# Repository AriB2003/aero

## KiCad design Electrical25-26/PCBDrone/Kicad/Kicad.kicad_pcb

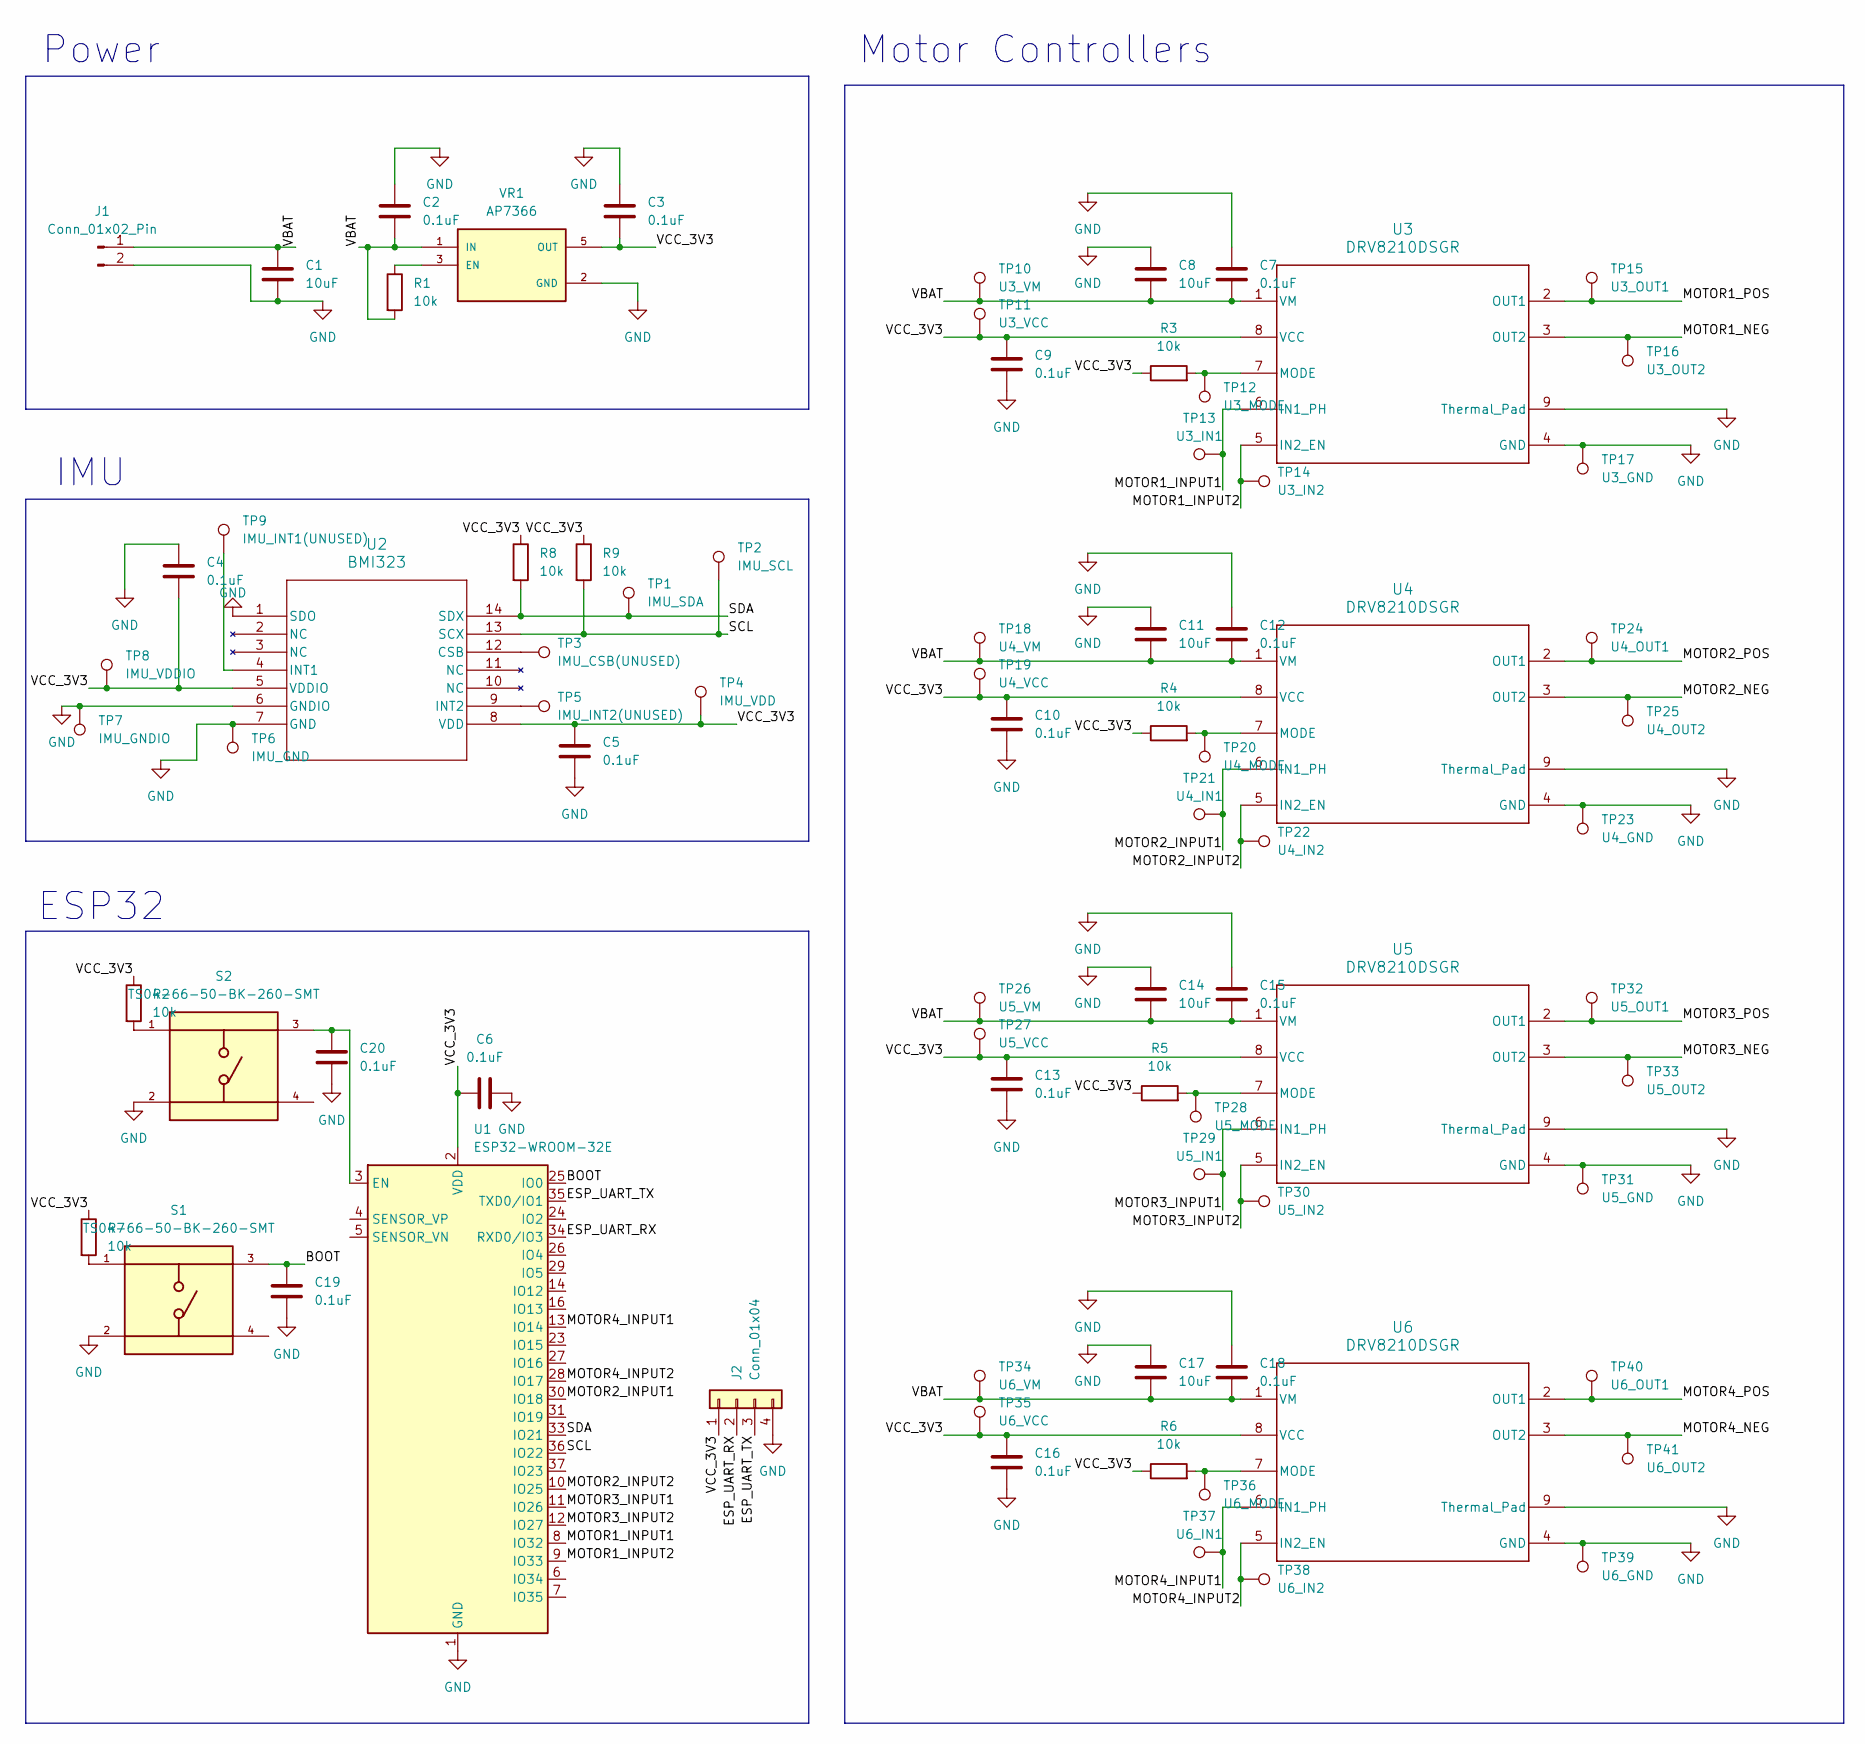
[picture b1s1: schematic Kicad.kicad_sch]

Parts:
C1, C8, C11, C14, C17: 10uF; C_0805_2012Metric
C2, C3, C4, C5, C6, C7, C9, C10, C12, C13, C15, C16, C18, C19, C20: 0.1uF; C_0603_1608Metric
J1: Conn_01x02_Pin; JST_B2B-PH-SM4-TB
J2: Conn_01x04; JST_B4B-PH-SM4-TB
R1, R2, R3, R4, R5, R6, R7, R8, R9: 10k; R_0603_1608Metric
S1, S2: TS04-66-50-BK-260-SMT; SW_TS04-66-50-BK-260-SMT; PARTREV 1.0
TP1: IMU_SDA; TestPoint_Pad_1.0x1.0mm
TP2: IMU_SCL; TestPoint_Pad_1.0x1.0mm
TP3: IMU_CSB(UNUSED); TestPoint_Pad_1.0x1.0mm
TP4: IMU_VDD; TestPoint_Pad_1.0x1.0mm
TP5: IMU_INT2(UNUSED); TestPoint_Pad_1.0x1.0mm
TP6: IMU_GND; TestPoint_Pad_1.0x1.0mm
TP7: IMU_GNDIO; TestPoint_Pad_1.0x1.0mm
TP8: IMU_VDDIO; TestPoint_Pad_1.0x1.0mm
TP9: IMU_INT1(UNUSED); TestPoint_Pad_1.0x1.0mm
TP10: U3_VM; TestPoint_Pad_1.0x1.0mm
TP11: U3_VCC; TestPoint_Pad_1.0x1.0mm
TP12: U3_MODE; TestPoint_Pad_1.0x1.0mm
TP13: U3_IN1; TestPoint_Pad_1.0x1.0mm
TP14: U3_IN2; TestPoint_Pad_1.0x1.0mm
TP15: U3_OUT1; TestPoint_Pad_1.0x1.0mm
TP16: U3_OUT2; TestPoint_Pad_1.0x1.0mm
TP17: U3_GND; TestPoint_Pad_1.0x1.0mm
TP18: U4_VM; TestPoint_Pad_1.0x1.0mm
TP19: U4_VCC; TestPoint_Pad_1.0x1.0mm
TP20: U4_MODE; TestPoint_Pad_1.0x1.0mm
TP21: U4_IN1; TestPoint_Pad_1.0x1.0mm
TP22: U4_IN2; TestPoint_Pad_1.0x1.0mm
TP23: U4_GND; TestPoint_Pad_1.0x1.0mm
TP24: U4_OUT1; TestPoint_Pad_1.0x1.0mm
TP25: U4_OUT2; TestPoint_Pad_1.0x1.0mm
TP26: U5_VM; TestPoint_Pad_1.0x1.0mm
TP27: U5_VCC; TestPoint_Pad_1.0x1.0mm
TP28: U5_MODE; TestPoint_Pad_1.0x1.0mm
TP29: U5_IN1; TestPoint_Pad_1.0x1.0mm
TP30: U5_IN2; TestPoint_Pad_1.0x1.0mm
TP31: U5_GND; TestPoint_Pad_1.0x1.0mm
TP32: U5_OUT1; TestPoint_Pad_1.0x1.0mm
TP33: U5_OUT2; TestPoint_Pad_1.0x1.0mm
TP34: U6_VM; TestPoint_Pad_1.0x1.0mm
TP35: U6_VCC; TestPoint_Pad_1.0x1.0mm
TP36: U6_MODE; TestPoint_Pad_1.0x1.0mm
TP37: U6_IN1; TestPoint_Pad_1.0x1.0mm
TP38: U6_IN2; TestPoint_Pad_1.0x1.0mm
TP39: U6_GND; TestPoint_Pad_1.0x1.0mm
TP40: U6_OUT1; TestPoint_Pad_1.0x1.0mm
TP41: U6_OUT2; TestPoint_Pad_1.0x1.0mm
U1: ESP32-WROOM-32E; ESP32-WROOM-32D
U2: BMI323; BMI323_BOS
U3, U4, U5, U6: DRV8210DSGR; DSG0008A-IPC_A
VR1: AP7366; AP7366-33W5-7; PARTREV 1-2

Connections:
/BOOT: C19.1, S1.3, U1.25 (IO0)
/ESP_UART_RX: J2.2, U1.34 (RXD0/IO3)
/ESP_UART_TX: J2.3, U1.35 (TXD0/IO1)
/MOTOR1_INPUT1: TP13.1, U1.8 (IO32), U3.6 (IN1_PH)
/MOTOR1_INPUT2: TP14.1, U1.9 (IO33), U3.5 (IN2_EN)
/MOTOR1_NEG: TP16.1, U3.3 (OUT2)
/MOTOR1_POS: TP15.1, U3.2 (OUT1)
/MOTOR2_INPUT1: TP21.1, U1.30 (IO18), U4.6 (IN1_PH)
/MOTOR2_INPUT2: TP22.1, U1.10 (IO25), U4.5 (IN2_EN)
/MOTOR2_NEG: TP25.1, U4.3 (OUT2)
/MOTOR2_POS: TP24.1, U4.2 (OUT1)
/MOTOR3_INPUT1: TP29.1, U1.11 (IO26), U5.6 (IN1_PH)
/MOTOR3_INPUT2: TP30.1, U1.12 (IO27), U5.5 (IN2_EN)
/MOTOR3_NEG: TP33.1, U5.3 (OUT2)
/MOTOR3_POS: TP32.1, U5.2 (OUT1)
/MOTOR4_INPUT1: TP37.1, U1.13 (IO14), U6.6 (IN1_PH)
/MOTOR4_INPUT2: TP38.1, U1.28 (IO17), U6.5 (IN2_EN)
/MOTOR4_NEG: TP41.1, U6.3 (OUT2)
/MOTOR4_POS: TP40.1, U6.2 (OUT1)
/SCL: R9.2, TP2.1, U1.36 (IO22), U2.13 (SCX)
/SDA: R8.2, TP1.1, U1.33 (IO21), U2.14 (SDX)
/VBAT: C1.1, C2.2, C7.2, C8.2, C11.2, C12.2, C14.2, C15.2, C17.2, C18.2, J1.1, R1.2, TP10.1, TP18.1, TP26.1, TP34.1, U3.1 (VM), U4.1 (VM), U5.1 (VM), U6.1 (VM), VR1.1 (IN)
/VCC_3V3: C3.2, C4.2, C5.1, C6.1, C9.1, C10.1, C13.1, C16.1, J2.1, R2.1, R3.1, R4.1, R5.1, R6.1, R7.1, R8.1, R9.1, TP4.1, TP8.1, TP11.1, TP19.1, TP27.1, TP35.1, U1.2 (VDD), U2.5 (VDDIO), U2.8 (VDD), U3.8 (VCC), U4.8 (VCC), U5.8 (VCC), U6.8 (VCC), VR1.5 (OUT)
GND: C1.2, C2.1, C3.1, C4.1, C5.2, C6.2, C7.1, C8.1, C9.2, C10.2, C11.1, C12.1, C13.2, C14.1, C15.1, C16.2, C17.1, C18.1, C19.2, C20.2, J1.2, J2.4, S1.2, S2.2, TP6.1, TP7.1, TP17.1, TP23.1, TP31.1, TP39.1, U1.1 (GND), U1.15 (GND), U1.38 (GND), U1.39 (GND), U2.1 (SDO), U2.6 (GNDIO), U2.7 (GND), U3.4 (GND), U3.9 (Thermal_Pad), U4.4 (GND), U4.9 (Thermal_Pad), U5.4 (GND), U5.9 (Thermal_Pad), U6.4 (GND), U6.9 (Thermal_Pad), VR1.2 (GND)
unnamed: R2.2, S2.1
unnamed: R7.2, S1.1
unnamed: C20.1, S2.3, U1.3 (EN)
unnamed: TP3.1, U2.12 (CSB)
unnamed: TP9.1, U2.4 (INT1)
unnamed: TP5.1, U2.9 (INT2)
unnamed: R3.2, TP12.1, U3.7 (MODE)
unnamed: R4.2, TP20.1, U4.7 (MODE)
unnamed: R5.2, TP28.1, U5.7 (MODE)
unnamed: R6.2, TP36.1, U6.7 (MODE)
unnamed: R1.1, VR1.3 (EN)

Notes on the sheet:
IMU
Motor Controllers
ESP32
Power

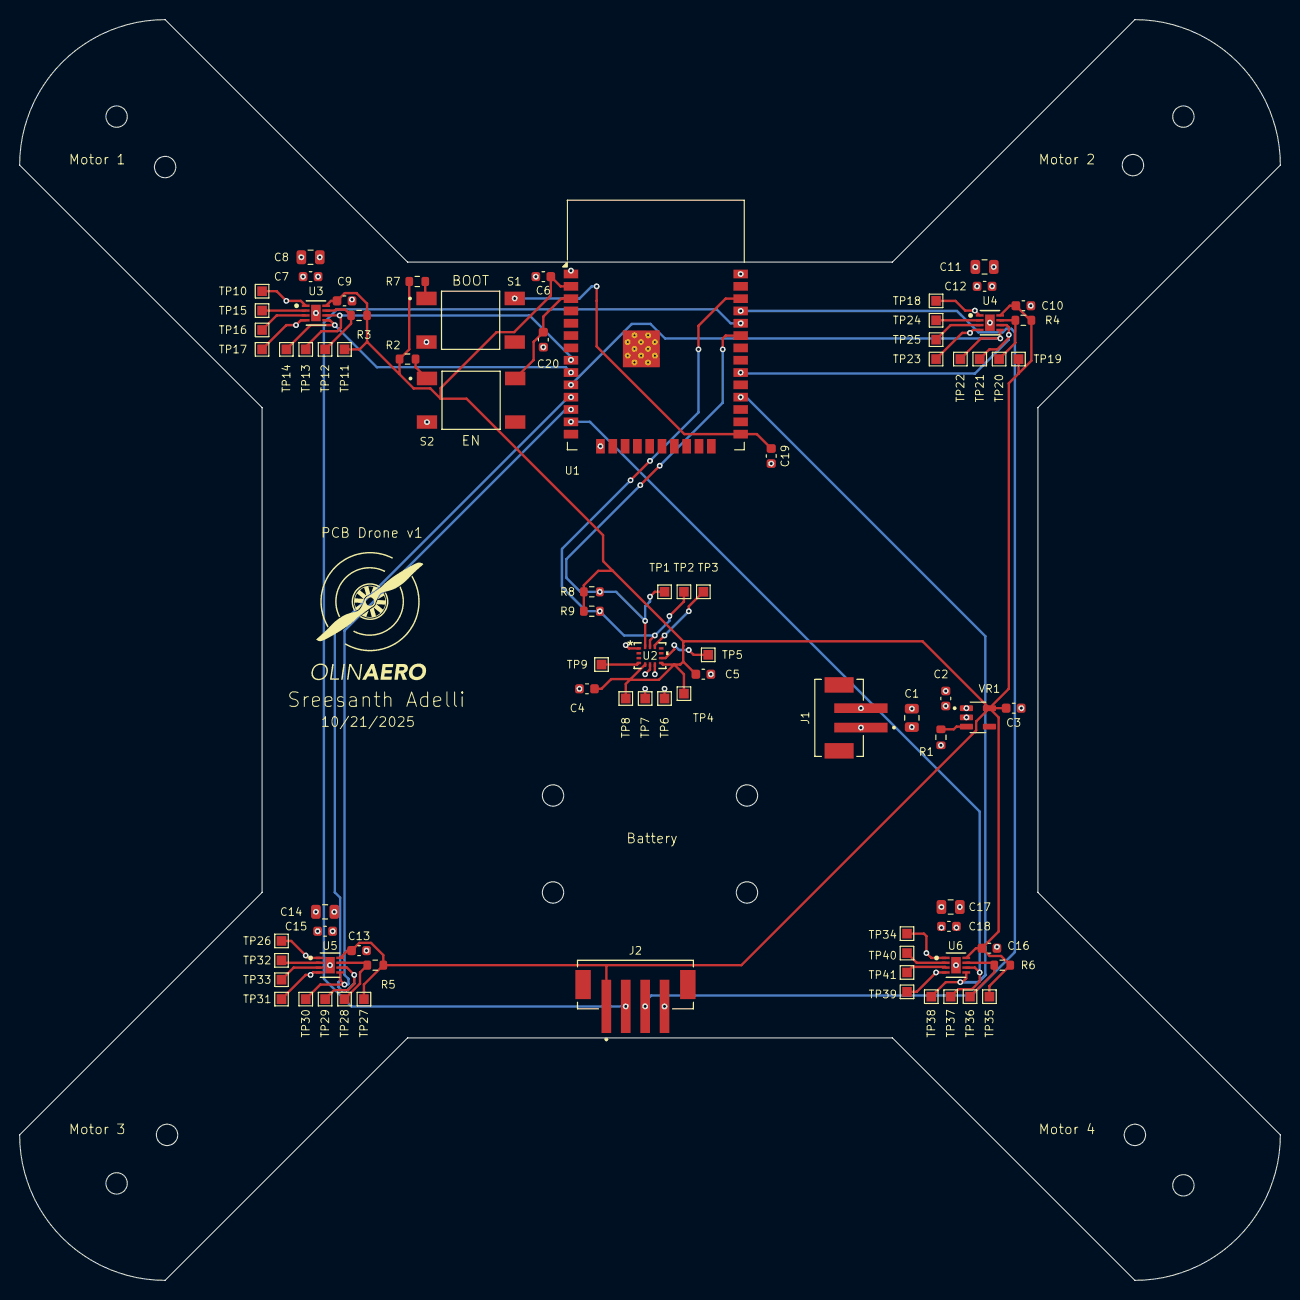
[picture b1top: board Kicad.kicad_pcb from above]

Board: 4 copper layers, 130.0 x 130.0 mm, 85 parts (0 on the bottom side), 35 nets.

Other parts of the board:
Motor Mount: Motor Mount; MotorMount
Motor Mount#2, Motor Mount#3, Motor Mount#4: Motor Mount; MotorMount

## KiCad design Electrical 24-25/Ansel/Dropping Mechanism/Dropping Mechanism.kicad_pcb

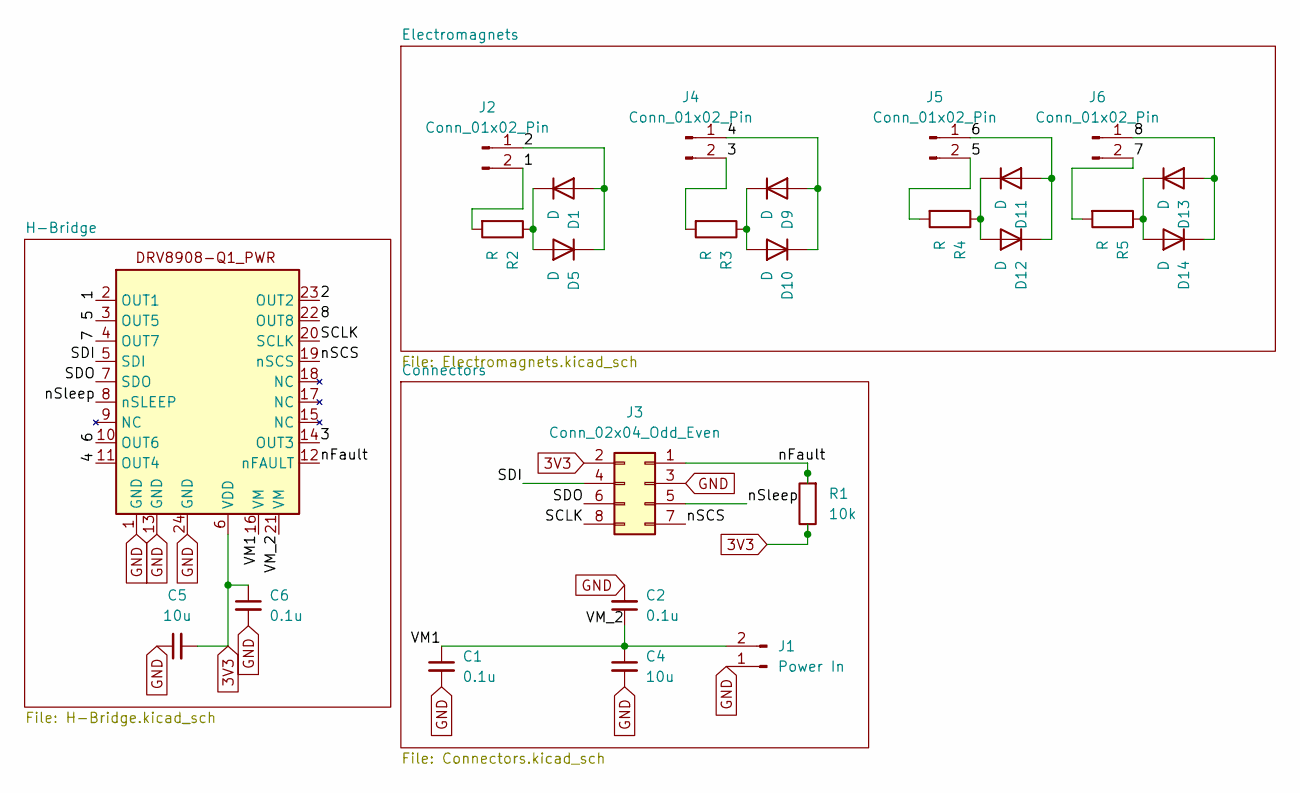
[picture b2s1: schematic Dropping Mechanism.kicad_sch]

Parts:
Automotive_Multi-Channel_Half-Bridge_Drivers_with_Advanced_Diagnostics2: HTSSOP-24-1EP_4.4x7.8mm_P0.65mm_EP3.4x7.8mm_Mask2.4x2.98mm
C1, C2, C6: 0.1u; C_0201_0603Metric
C4, C5: 10u; C_0201_0603Metric
D1, D5, D9, D10, D11, D12, D13, D14: D
J1: Power In; AMASS_XT60PW-M_1x02_P7.20mm_Horizontal
J2, J4, J5, J6: Conn_01x02_Pin; JST_XH_B2B-XH-AM_1x02_P2.50mm_Vertical
J3: Conn_02x04_Odd_Even; PinHeader_2x04_P2.54mm_Vertical
R1: 10k; R_0201_0603Metric
R2, R3, R4, R5: R

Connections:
3V3: Automotive_Multi-Channel_Half-Bridge_Dr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.6 (VDD), C5.2, C6.1, J3.2, R1.1
/1: Automotive_Multi-Channel_Half-Bridge_Dr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.2 (OUT1), J2.2, R2.2; also elsewhere on the board
/2: Automotive_Multi-Channel_Half-Bridge_Dr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.23 (OUT2), D1.2 (A), D5.1 (K), J2.1
/3: Automotive_Multi-Channel_Half-Bridge_Dr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.14 (OUT3), J4.2, R3.2
/4: Automotive_Multi-Channel_Half-Bridge_Dr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.11 (OUT4), D9.2 (A), D10.1 (K), J4.1
/5: Automotive_Multi-Channel_Half-Bridge_Dr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.3 (OUT5), J5.2, R4.2
/6: Automotive_Multi-Channel_Half-Bridge_Dr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.10 (OUT6), D11.2 (A), D12.1 (K), J5.1
/7: Automotive_Multi-Channel_Half-Bridge_Dr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.4 (OUT7), J6.2, R5.2
/8: Automotive_Multi-Channel_Half-Bridge_Dr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.22 (OUT8), D13.2 (A), D14.1 (K), J6.1
/SCLK: Automotive_Multi-Channel_Half-Bridge_Dr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.20 (SCLK), J3.8
/SDI: Automotive_Multi-Channel_Half-Bridge_Dr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.5 (SDI), J3.4
/SDO: Automotive_Multi-Channel_Half-Bridge_Dr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.7 (SDO), J3.6
/VM1: Automotive_Multi-Channel_Half-Bridge_Dr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.16 (VM), Automotive_Multi-Channel_Half-Bridge_Dr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.21 (VM), C1.1, C2.1, C4.1, J1.2
/nFault: Automotive_Multi-Channel_Half-Bridge_Dr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.12 (nFAULT), J3.1, R1.2
/nSCS: Automotive_Multi-Channel_Half-Bridge_Dr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.19 (nSCS), J3.7
/nSleep: Automotive_Multi-Channel_Half-Bridge_Dr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.8 (nSLEEP), J3.5
GND: Automotive_Multi-Channel_Half-Bridge_Dr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.1 (GND), Automotive_Multi-Channel_Half-Bridge_Dr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.13 (GND), Automotive_Multi-Channel_Half-Bridge_Dr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.24 (GND), C1.2, C2.2, C4.2, C5.1, C6.2, J1.1, J3.3
unnamed 17: D1.1 (K), D5.2 (A), R2.1; also elsewhere on the board
unnamed: D9.1 (K), D10.2 (A), R3.1
unnamed: D11.1 (K), D12.2 (A), R4.1
unnamed: D13.1 (K), D14.2 (A), R5.1

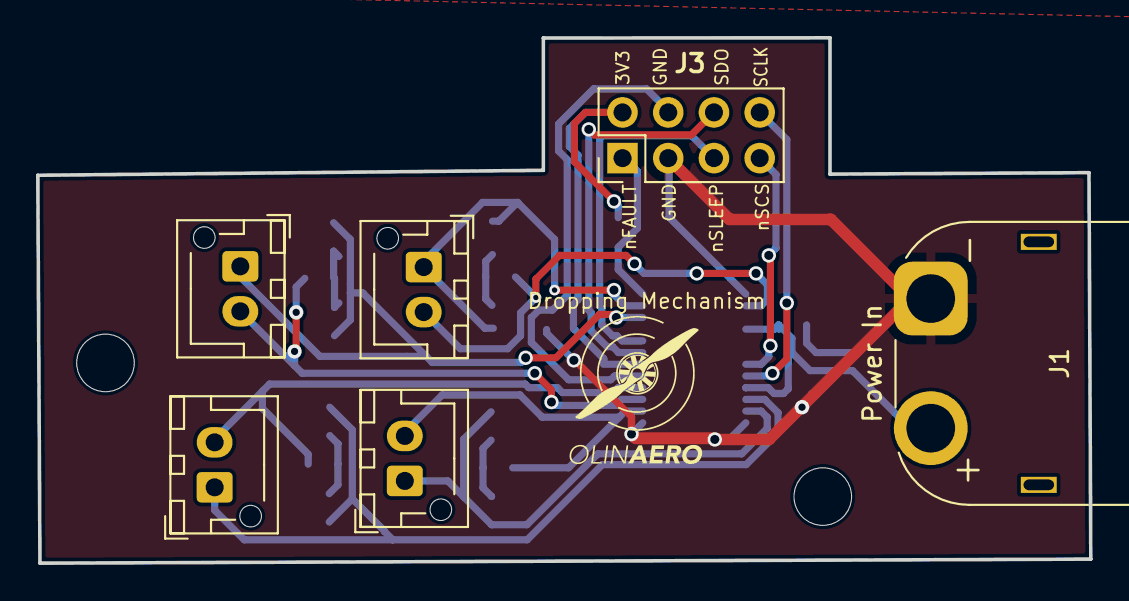
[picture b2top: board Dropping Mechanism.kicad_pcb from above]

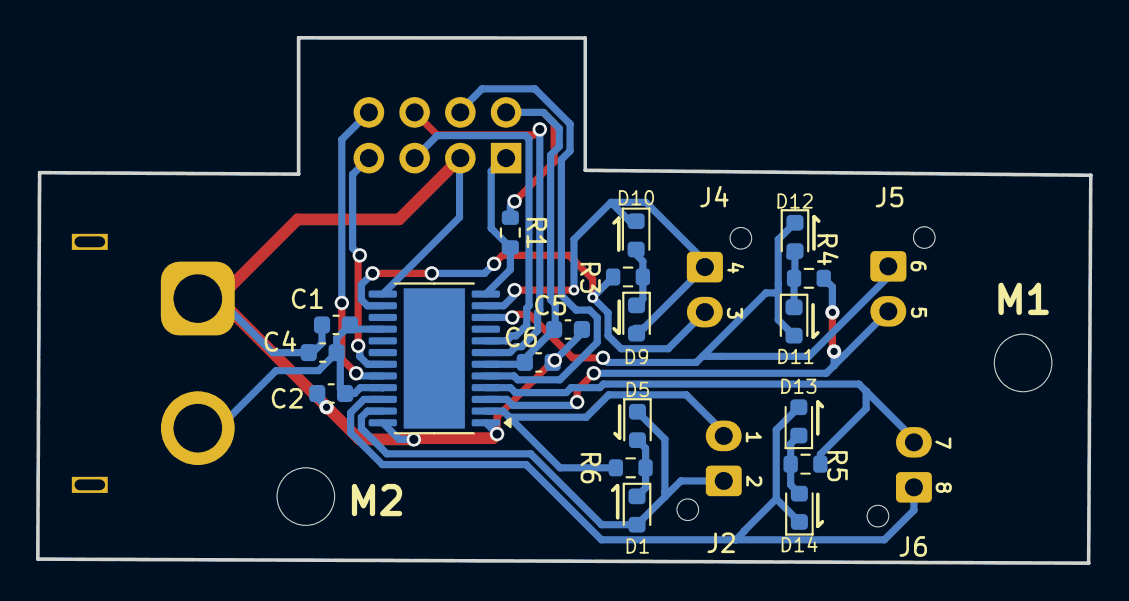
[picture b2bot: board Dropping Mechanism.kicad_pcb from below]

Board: 2 copper layers, 58.5 x 29.2 mm, 25 parts (19 on the bottom side), 21 nets.

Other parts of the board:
R6: 0.65k; R_0603_1608Metric

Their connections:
/1: R6.2; also elsewhere on the board
unnamed 17: R6.1; also elsewhere on the board

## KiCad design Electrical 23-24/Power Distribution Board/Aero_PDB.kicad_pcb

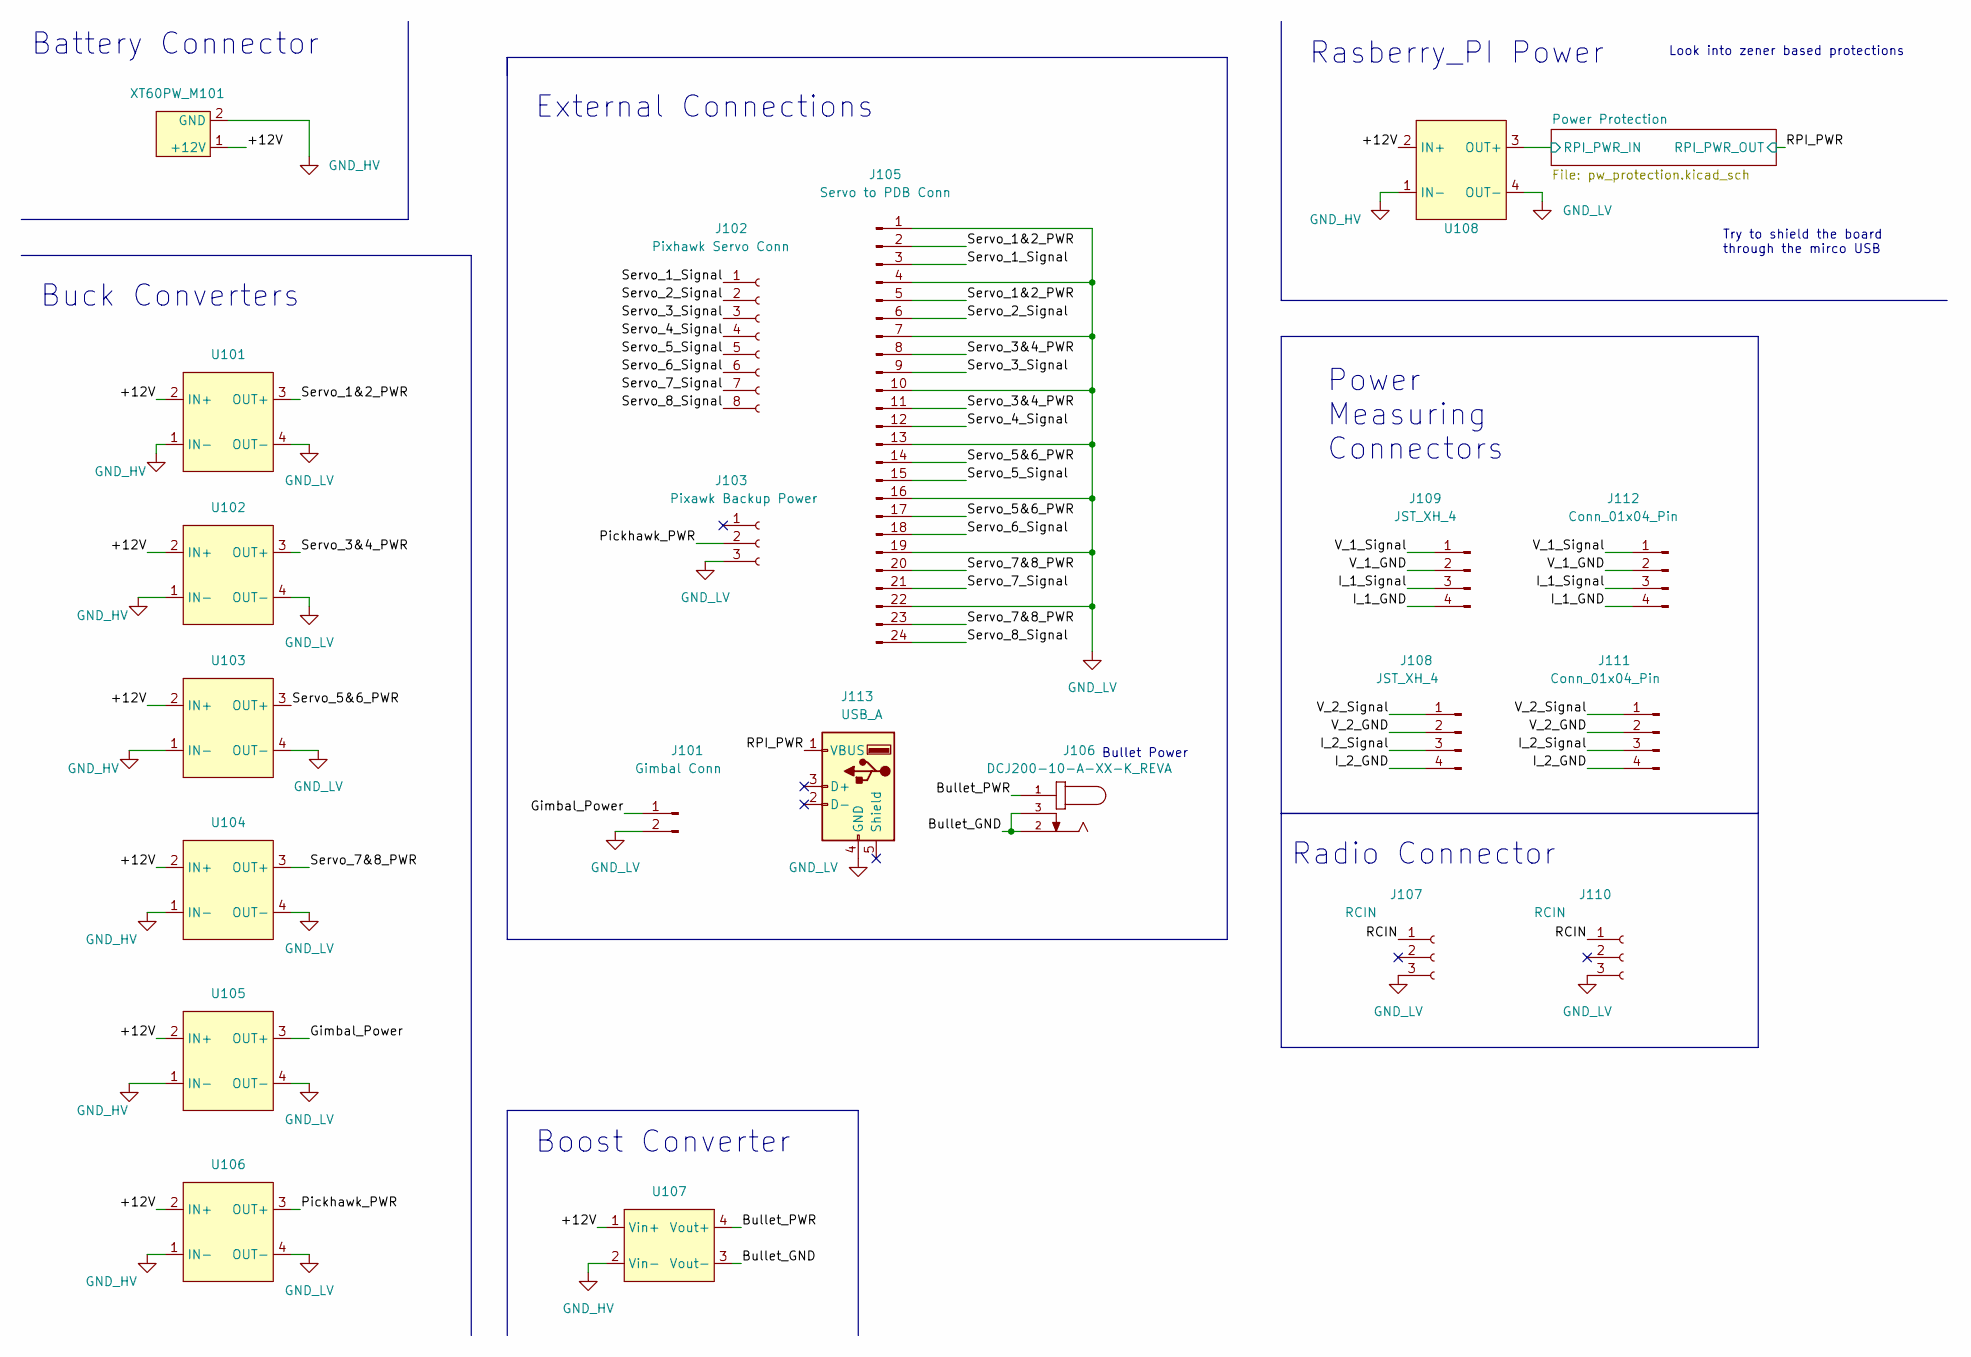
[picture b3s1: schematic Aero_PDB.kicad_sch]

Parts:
J101: Gimbal Conn; JST_XH_B2B-XH-A_1x02_P2.50mm_Vertical
J102: Pixhawk Servo Conn; PinHeader_1x08_P2.54mm_Vertical
J103: Pixawk Backup Power; PinHeader_1x03_P2.54mm_Vertical
J105: Servo to PDB Conn; SAMTEC_TSW-108-07-G-T
J106: DCJ200-10-A-XX-K_REVA; GCT_DCJ200-10-A-XX-K_REVA; PARTREV A
J107, J110: RCIN; PinHeader_1x03_P2.54mm_Vertical
J108, J109: JST_XH_4; JST_XH_B4B-XH-A_1x04_P2.50mm_Vertical
J111, J112: Conn_01x04_Pin; PinHeader_1x04_P2.54mm_Vertical
J113: USB_A; GCT_USB1130-15-A_REVA
U101, U102, U103, U104, U105, U106, U108: YAAJ_DCDC_StepDown_LM2596
U107: MT3608_module
XT60PW_M101: AMASS_XT60PW-F

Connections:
/+12V: U101.2 (IN+), U102.2 (IN+), U103.2 (IN+), U104.2 (IN+), U105.2 (IN+), U106.2 (IN+), U107.1 (Vin+), U108.2 (IN+), XT60PW_M101.1 (+12V)
/Bullet_GND: J106.2, J106.3, U107.3 (Vout-)
/Bullet_PWR: J106.1, U107.4 (Vout+)
/Gimbal_Power: J101.1, U105.3 (OUT+)
/I_1_GND: J109.4, J112.4
/I_1_Signal: J109.3, J112.3
/I_2_GND: J108.4, J111.4
/I_2_Signal: J108.3, J111.3
/Pickhawk_PWR: J103.2, U106.3 (OUT+)
/Power Protection /RPI_PWR_IN: U108.3 (OUT+); also elsewhere on the board
/RCIN: J107.1, J110.1
/RPI_PWR: J113.1 (VBUS); also elsewhere on the board
/Servo_1&2_PWR: J105.2, J105.5, U101.3 (OUT+)
/Servo_1_Signal: J102.1, J105.3
/Servo_2_Signal: J102.2, J105.6
/Servo_3&4_PWR: J105.8, J105.11, U102.3 (OUT+)
/Servo_3_Signal: J102.3, J105.9
/Servo_4_Signal: J102.4, J105.12
/Servo_5&6_PWR: J105.14, J105.17, U103.3 (OUT+)
/Servo_5_Signal: J102.5, J105.15
/Servo_6_Signal: J102.6, J105.18
/Servo_7&8_PWR: J105.20, J105.23, U104.3 (OUT+)
/Servo_7_Signal: J102.7, J105.21
/Servo_8_Signal: J102.8, J105.24
/V_1_GND: J109.2, J112.2
/V_1_Signal: J109.1, J112.1
/V_2_GND: J108.2, J111.2
/V_2_Signal: J108.1, J111.1
GND1: U101.1 (IN-), U102.1 (IN-), U103.1 (IN-), U104.1 (IN-), U105.1 (IN-), U106.1 (IN-), U107.2 (Vin-), U108.1 (IN-), XT60PW_M101.2 (GND)

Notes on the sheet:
Try to shield the board through the mirco USB
Boost Converter
External Connections
Battery Connector
Look into zener based protections
Bullet Power
Radio Connector
Rasberry_PI Power
Power Measuring Connectors
Buck Converters

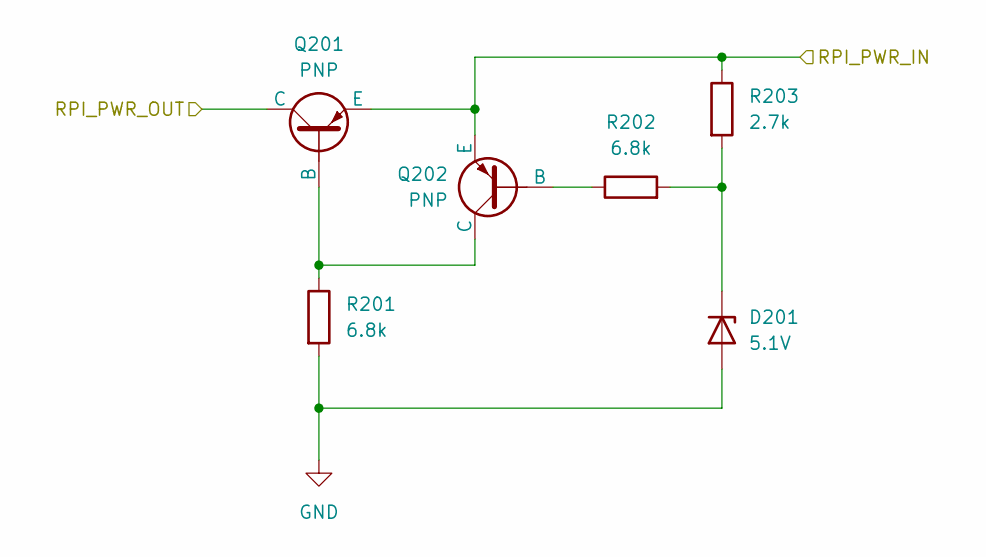
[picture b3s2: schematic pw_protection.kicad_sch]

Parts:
D201: 5.1V; SOD1608X70
Q201, Q202: PNP; SOT-23-3_1P4X3P040_ONS
R201, R202: 6.8k; R_0603_1608Metric
R203: 2.7k; R_0603_1608Metric

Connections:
/Power Protection /RPI_PWR_IN: Q201.3 (E), Q202.3 (E), R203.1; also elsewhere on the board
/RPI_PWR: Q201.1 (C); also elsewhere on the board
unnamed: D201.1 (K), R202.2, R203.2
unnamed: Q201.2 (B), Q202.1 (C), R201.1
unnamed: Q202.2 (B), R202.1

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
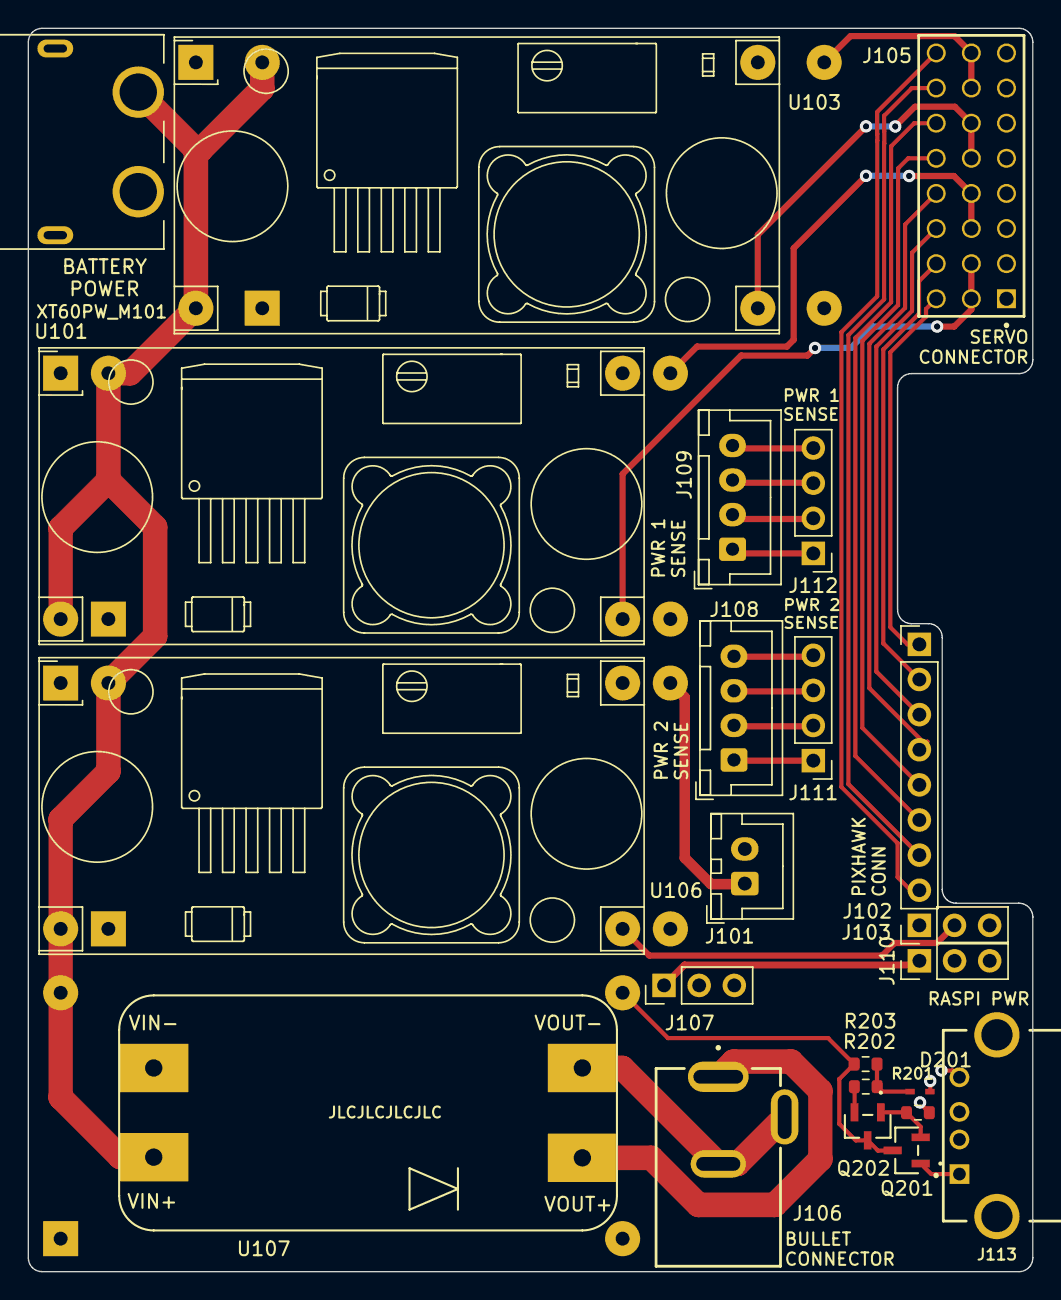
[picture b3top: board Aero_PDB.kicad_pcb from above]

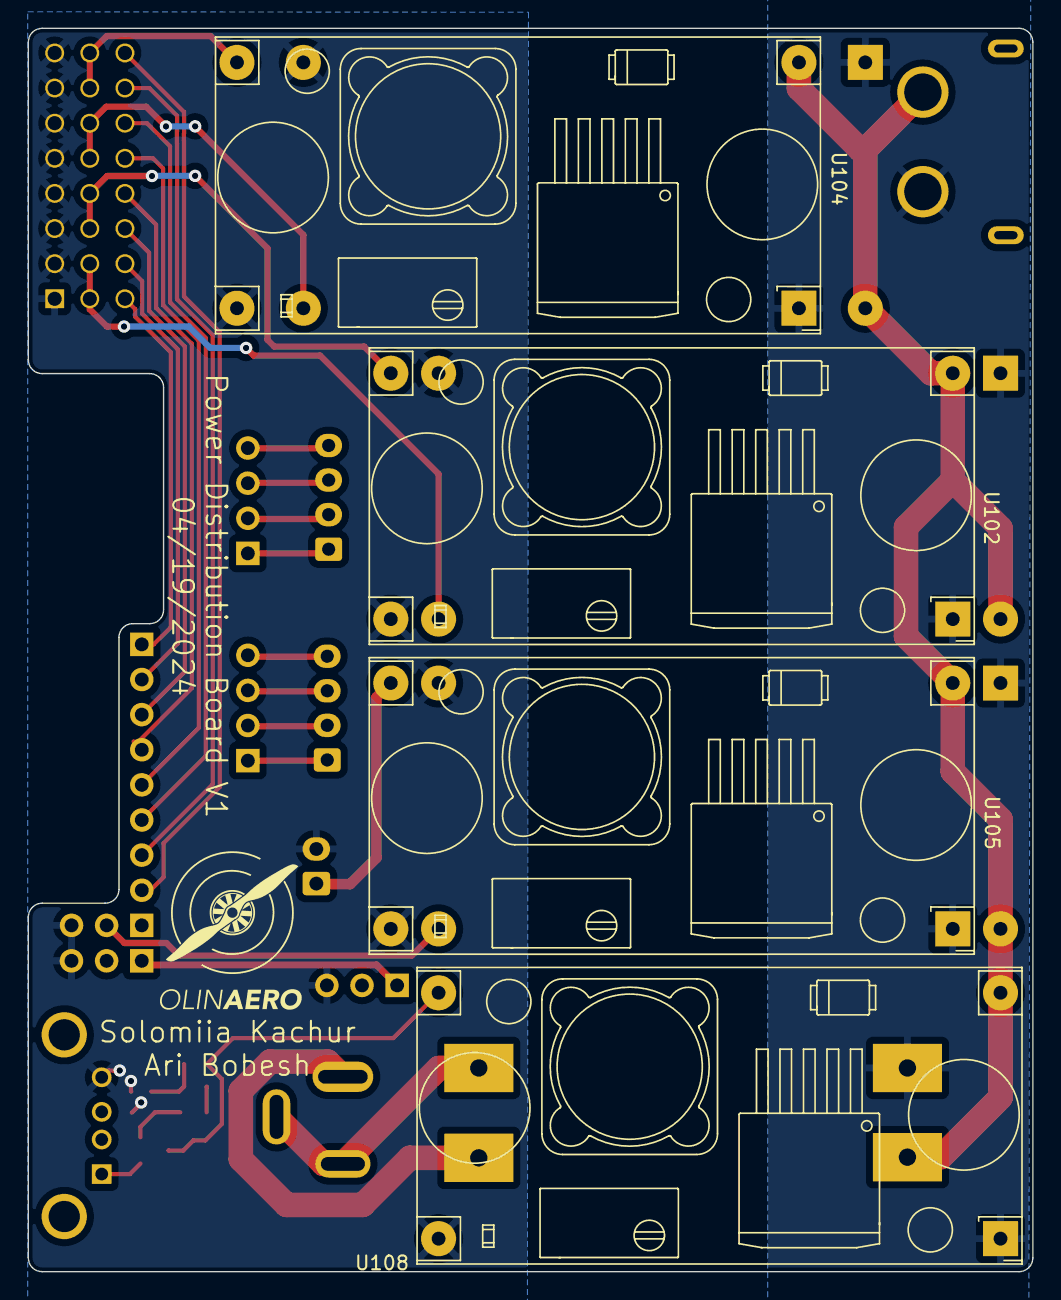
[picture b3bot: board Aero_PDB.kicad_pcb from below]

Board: 2 copper layers, 72.6 x 89.9 mm, 27 parts (4 on the bottom side), 33 nets.
